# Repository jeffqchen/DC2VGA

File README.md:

# DC2VGA

An SD/VGA RGBS/RGBHV Switchable Dongle for Sega Dreamcast.

This belongs to my [series of VGA adapters](https://github.com/jeffqchen/Console-VGA-Dongle-Series) for various retro consoles and video equipments.

This adapter plugs into the AV OUT port on a Sega Dreamcast and allows you to out put RGBS or RGBHV video signal, as well as a stereo audio signal.

------------
## Usage

### Toggling Modes

There are two independent toggle switches on this dongle for choosing different modes.

- SD / VGA allows you to choose between 525i (SD) and 525p (VGA) RGB output
- CSYNC / HV allows you to choose between attenuated CSync and 3.3V H/V-Sync

I have tested this dongle with various devices:

|              | SD+CSync | VGA+CSync | SD+HV  | VGA+HV    |
|--------------|----------|-----------|--------|-----------|
| RetroTINK 5X | **Yes**  | **Yes**   | No     | No        |
| OSSC (AV3)   | Yes*     | **Yes**   | **Yes**| **Yes**   |
| GBS Control  | **Yes**  | **Yes**   | Yes*   | Yes*      |
| PVM/BVM      | **Yes**  | [*Maybe*](https://github.com/jeffqchen/DC2VGA#combined-csync)  | No     | No        |
| PC Monitors  | No       | No        | No     | **Yes**   |

The No ones are mostly device limitations and not a problem with the dongle itself.

The Yes* ones means they only work when the signal first went through an Extron switch. It's probably that the switch reconditioned the signals in some way to overcome the limitations of these devices and made things work. A direct connection does not work in these cases and it's expected.

The only real compatibility issue I've encountered so far, is **VGA** mode + **CSync** on Sony BVM D series. This BVM doesn't like combined CSync and will not display it properly. **However it will work properly in SD mode.**

#### *VGA Trick*

*(Bust-A-Move 4 tricked into run in VGA mode)*

Some games that require an SD cable can be forced into VGA mode by toggling the top switch from SD to VGA, right after booting up the game (at the VMU beep or right after game started from the ODE).

### Audio

Audio can be carried inside the VGA cable as-is, or extracted from the 3.5mm jack on the dongle.

* *Buzzing may be noticeable when audio is transmitted within the VGA cable in certain scenes in certain games. This is due to insufficient shielding in most VGA cables. If you find the buzzing to be annoying, use the 3.5mm jack on the dongle for audio output. This will ensure the cleanest possible audio.*

### Other Use Cases

Light guns work if you output to a CRT display (TV and PC monitor).

 -----------

 ## Parts

- PCB (You need both)
  - [Vertical PCB](https://oshpark.com/shared_projects/WcKgCnij)
  - [Horizontal PCB](https://oshpark.com/shared_projects/jPAbQ0ej)

- [1x] Dreamcast AV Plugs - [Link](https://github.com/jeffqchen/JeffParts/blob/main/Connectors/Dreamcast%20AV%20Plug/info.md)

- [2x] Toggle Switches (SW1 & SW2) - [Link](https://github.com/jeffqchen/JeffParts/tree/main/Switches/EG2208%20Toggle%20Switch/info.md)
  - *If you want slightly longer switch stems, use **EG2208A** instead.*

- [1x] VGA Port Slim Female - [Link](https://github.com/jeffqchen/JeffParts/blob/main/Connectors/HD15/Slim/Female%20PCB/info.md)

- [1x] 3.5mm Headphone Jack - [Link](https://github.com/jeffqchen/JeffParts/blob/main/Connectors/3.5mm%20Audio%20Jack/Vertical%205-Pin%20PCB/info.md)

- [1x] M2x20mm screw and hex nut - [Link](https://github.com/jeffqchen/JeffParts/blob/main/Parts/M2%20M3%20Hex%20Screw%20%26%20Nut/info.md)

- 2.54mm-Pitched Right Angle Pin Header (at least 11-pin wide) - [Link](https://github.com/jeffqchen/JeffParts/blob/main/Connectors/Pin%20Header/2.54mm%20Pitch/Male%20Right-Angle/info.md)

### SMD Components

*All SMD resistors and capacitors are in imperial 0603 size unless specified otherwise*

#### On Vertical Board
- **U1**: [1x] 4-Channel XOR Logic Gate, 14TSSOP
  - MC74HC86ADTR2G Quad XOR Gate - [[Link](https://github.com/jeffqchen/JeffParts/blob/main/Components/MC74HC86ADTR2G%20Quad%20XOR%20Gate/info.md)]
- **C1 C2 C3**: [3x] 220uF / 6.3V / **Imperial 1206 Size** - [[Link](https://github.com/jeffqchen/JeffParts/blob/main/Components/220uF%20SMD%20Cap/info.md)]
- **C4**: [1x] 0.1uF / 10V
- **C5 C6**: [2x] ]1uF / 10V
- **R1 R2**: [2x] 150 Ohm
- **R3 R4**: [2x] 10K Ohm

**R5 and R6** can have different configurations. Choose one from the following:
- For 0.6V Vpp CSync: (common attenuated CSync level)
  - R5: 25 Ohm
  - R6: 680 Ohm

- For 0.3V Vpp CSync: (SCART-safe sync level)
  - R5: 75 Ohm
  - R6: 1K Ohm

#### On Horizontal Board
- C1 C2: [2x] 10uF / 6.3V

-----------

## 3D Printing

Print all parts in their original orientations.

The shells are printed on the 3.5mm port side to give it a flat surface on that side and better details on the top.

Try using tree support as it's easier to extract and leaves less damage to up-facing surfaces below supported surfaces.

Make sure all support material is removed before trying to fit the electronics inside, as there is zero space to spare inside.

### Without A Shell

Thanks to [Retro Gamer Stuff](https://twitter.com/RetroGamerStuff)'s suggestion, I've adopted right-angle pin headers to interconnect the two PCBs with a very reliable connection. This means the internal assembly should be able to sustain even without a shell. It will be unsightly, but should be strong enough regardless.

-----------

## Preparations

### Dreamcast Video Plug

The original Dreamcast video plug has a cross bar to prevent the pins from falling out. You need to extract it with a side cutter or dental pick like shown in the picture. Try prying from the center of the bar so it lifts cleanly.

*IF* a pin falls out during the process, simply carefully push it back into its original place.

Put the printed "Plug Helper" piece over the pins. Note the correct side of the slot. Then push it all the way into the back of the plug until it's flush.

This piece helps to maintain a leveled surface so the plug can be soldered to the PCB reliably.

### PCB

Trim extra tabs sticking outside from the PCB outline with a side-cutter and file. Otherwise you may run into issues trying to fit the assembly into the 3D printed shell.

-----------

## Assembly

Populate the horizontal and vertical PCBs with all of the SMD components first.

Solder in the Dreamcast video plug and the switches onto the "DC Side" of the vertical board.

Note the DC video plug should be perpendicular to the vertical PCB.

There is an area of exposed copper next to the DC video plug. You can add some solder in this area to further strengthen the connection between the plug and the PCB. However it's only optional.

Cut a section of the pin header with 11 pins. Fit the bent end onto the horizontal PCB from the bottom side, as close as possible. Then solder in the two ends first.

You can adjust the pin header by melting the two ends. Make sure the straight part of the pin header is parallel to the PCB as much as possible.

Now start trimming out the extra length of the pins on the bent end. Make it as flush as possible to the PCB. Do the unsoldered pins in the middle first, then solder the flush pins to the PCB.

Lastly, suck up any excessive solder from the two end pins, and then trim them flush as well.

Using a cutter, cut and remove the black plastic piece that holds all the pins together. Try cutting in with a light angle so the cuts reach the pins for an easy removal.

Now solder in the VGA and 3.5mm port tightly onto the horizontal PCB.

Trim the 3 pins that would be blocked by the toggle switch. Refer to the photos for an easier way to get it done.

Temporarily fit the entire assembly into the top shell. Position the PCBs so the 3.5mm port and VGA port fits into the cutouts on the top shell snugly, and the vertical PCB is as vertical as possible.

 Solder the 3 trimmed pins and the one on the other end, to hold the assembly together.

Take the assembly out of the 3D printed shell. We do NOT want to do a lot of soldering when the assembly is inside the shell, or the heat may damage it.

Go on and trim all the rest of the excessive straight pins and solder them in place. Feed an ample amount of solder and heat up the pin long enough so the solder could seep into the vias on the vertical PCB.

Inspect the other side and make sure the vias are filled by solder. If not, heat it up again with a bit more solder. The internal assembly is now finished.

Now, fit the completed internals into the bottom shell, then put the top shell over it and close it up.

Secure the shells with a set of M2x20mm screw and nut.

------------
## Some Technical Nuances

### Native CSync

This Dongle uses the native CSync signal generated by the Dreamcast itself - when it's set to SD mode. This mode has the best compatibility with SD TVs and monitors.

### Combined CSync

When set to VGA mode **AND** CSync, the circuit inside uses an XOR logic chip to combine the native HSync and VSync signals into an artificial CSync signal. This signal has a slight discrepancy from a standard CSync signal, and some equipments that rely on PLL (phase lock loop) would be thrown off (as documented in the [HDRetrovision Blog](https://www.hdretrovision.com/blog/2019/10/10/engineering-csync-part-2-falling-short)).

This issue was anticipated and since in most cases, you would not run into any issue, I opted to not dig deeper and further complicate the design.

#### Proper Sync Combining

However, if you are stuck with a rare display that absolutely requires proper sync combining, you may look into Extron's RGB 19X line of product.

They feature proper sync combining with serration. This will fix the CSync issue IF your device refuse to work with the rough method. At this moment, it's only listed for around $30 on eBay. It's a very good value in my personal opinion, as this device can work with a various range of VGA devices and resolutions.

Set the DC2VGA to "HV" mode, connect the VGA cable to the Extron RGB, set SERR and DDSP to the UP position, connect the BNC cables to the R/G/B/S ports on the back, and the issue should be fixed.

*The audio adapter in the 2nd photo is my [Extron Audio 3.5mm Adapter](https://github.com/jeffqchen/Extron-Audio-3.5mm-Adapter).*

### OSSC AV3 Input Limitations

The AV3 input on the OSSC require clean TTL-level sync signals. However the native CSync output from the Dreamcast is an attenuated one. This signal does not work with the OSSC and is expected.

*Source: [OSSC Wiki](https://junkerhq.net/xrgb/index.php/OSSC#AV3_.28VGA.29)*

### GBS Control Limitations
The GBS 82XX board does not work nicely with VGA signals. [Robert Neumann](https://twitter.com/_ramapcsx2) put in some time hoping to make it work but decided it's not a suitable use case for the GBS board. So the RGBHV signal coming from the Dreamcast not working with GBS is expect. You should always use CSync instead.

### Improved Compatibility with Extron switches
By running the signal through an Extron MVX Switch, several of the incompatibilities mentioned above could be overcome. It probably thanks to the extra signal conditioning it performances on the inside. These Extron devices are lovely.

**But you should always remember that they output 5V TTL sync and that needs to be properly attenuated if connected to a consumer device.**

-----------
## Special Thanks
Mike Chi
- Twitter: https://twitter.com/retrotink2
- Official Website: https://www.retrotink.com/

HDRetrovision
- Twitter: https://twitter.com/hdretrovision
- Official Website: https://www.hdretrovision.com/

Javier Rodas
- Twitter: https://twitter.com/JaviRodasG

Robert Neumann
- Twitter: https://twitter.com/_ramapcsx2

Retro Gamer Stuff (Bad_Ad84)
- https://twitter.com/RetroGamerStuff

-----------
Shield: [![CC BY-SA 4.0][cc-by-sa-shield]][cc-by-sa]

This work is licensed under a
[Creative Commons Attribution-ShareAlike 4.0 International License][cc-by-sa].

[![CC BY-SA 4.0][cc-by-sa-image]][cc-by-sa]

[cc-by-sa]: http://creativecommons.org/licenses/by-sa/4.0/
[cc-by-sa-image]: https://licensebuttons.net/l/by-sa/4.0/88x31.png
[cc-by-sa-shield]: https://img.shields.io/badge/License-CC%20BY--SA%204.0-lightgrey.svg

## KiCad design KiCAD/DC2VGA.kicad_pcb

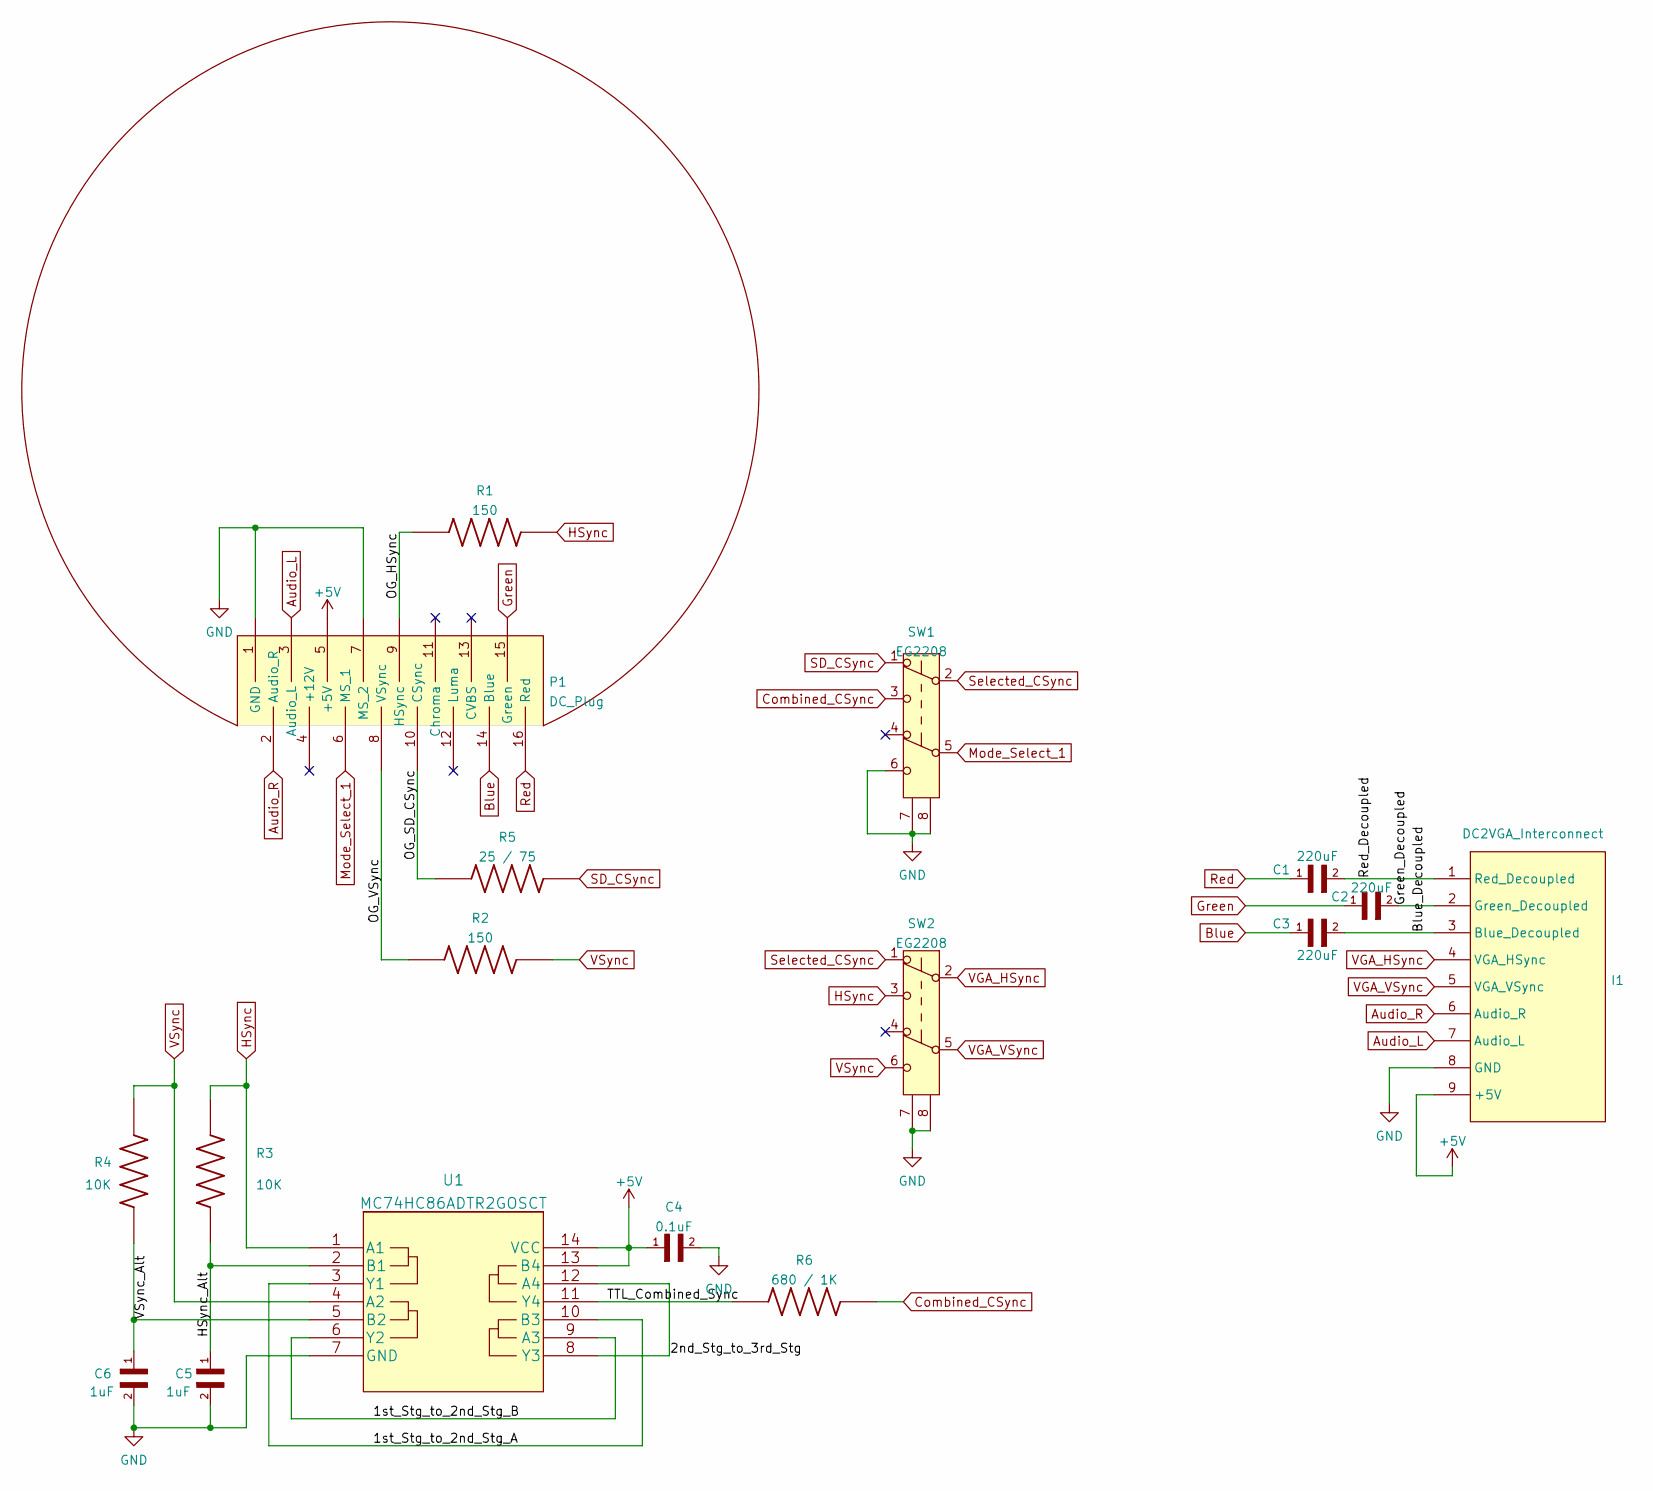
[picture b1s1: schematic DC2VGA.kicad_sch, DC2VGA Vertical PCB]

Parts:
C1, C2, C3: 220uF; Cap_SMD_1206
C4: 0.1uF; C_0603_1608Metric
C5, C6: 1uF; C_0603_1608Metric
I1: DC2VGA_Interconnect; DC_Interconnect_Vertical
P1: DC_Plug
R1, R2: 150; R_0603_1608Metric
R3, R4: 10K; R_0603_1608Metric
R5: 25 / 75; R_0603_1608Metric
R6: 680 / 1K; R_0603_1608Metric
SW1, SW2: EG2208; EG2208_DPDT_Switch
U1: MC74HC86ADTR2GOSCT; MC74HC86

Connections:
+5V: C4.1, I1.9 (+5V), P1.5 (+5V), U1.13 (B4), U1.14 (VCC)
/1st_Stg_to_2nd_Stg_A: U1.3 (Y1), U1.10 (B3)
/1st_Stg_to_2nd_Stg_B: U1.6 (Y2), U1.9 (A3)
/2nd_Stg_to_3rd_Stg: U1.8 (Y3), U1.12 (A4)
/Blue_Decoupled: C3.2, I1.3 (Blue_Decoupled)
/Green_Decoupled: C2.2, I1.2 (Green_Decoupled)
/HSync_Alt: C5.1, R3.1, U1.2 (B1)
/OG_Combined_Sync: R6.1, U1.11 (Y4)
/OG_HSync: P1.9 (HSync), R1.1
/OG_SD_CSync: P1.10 (CSync), R5.1
/OG_VSync: P1.8 (VSync), R2.1
/Red_Decoupled: C1.2, I1.1 (Red_Decoupled)
/VSync_Alt: C6.1, R4.2, U1.5 (B2)
Audio_L: I1.7 (Audio_L), P1.3 (Audio_L)
Audio_R: I1.6 (Audio_R), P1.2 (Audio_R)
Blue: C3.1, P1.14 (Blue)
Combined_CSync: R6.2, SW1.3 (C)
GND: C4.2, C5.2, C6.2, I1.8 (GND), P1.1 (GND), P1.7 (MS_2), SW1.6 (C), SW1.7 (Shield), SW1.8 (GND), SW2.7 (Shield), SW2.8 (GND), U1.7 (GND)
Green: C2.1, P1.15 (Green)
HSync: R1.2, R3.2, SW2.3 (C), U1.1 (A1)
Mode_Select_1: P1.6 (MS_1), SW1.5 (B)
Red: C1.1, P1.16 (Red)
SD_CSync: R5.2, SW1.1 (A)
Selected_CSync: SW1.2 (B), SW2.1 (A)
VGA_HSync: I1.4 (VGA_HSync), SW2.2 (B)
VGA_VSync: I1.5 (VGA_VSync), SW2.5 (B)
VSync: R2.2, R4.1, SW2.6 (C), U1.4 (A2)

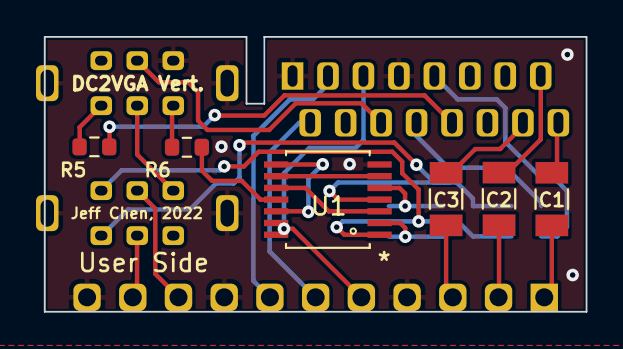
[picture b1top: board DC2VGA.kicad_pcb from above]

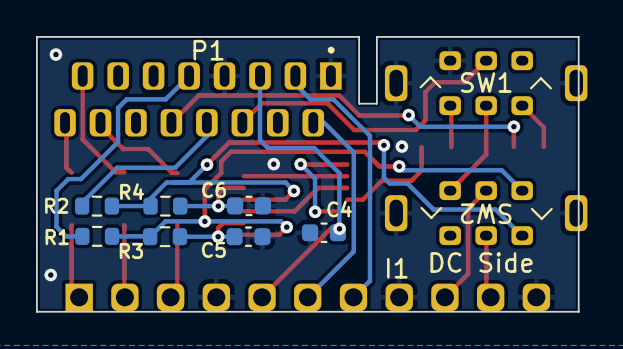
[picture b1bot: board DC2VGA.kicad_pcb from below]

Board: 2 copper layers, 30.1 x 15.3 mm, 17 parts (11 on the bottom side), 27 nets.

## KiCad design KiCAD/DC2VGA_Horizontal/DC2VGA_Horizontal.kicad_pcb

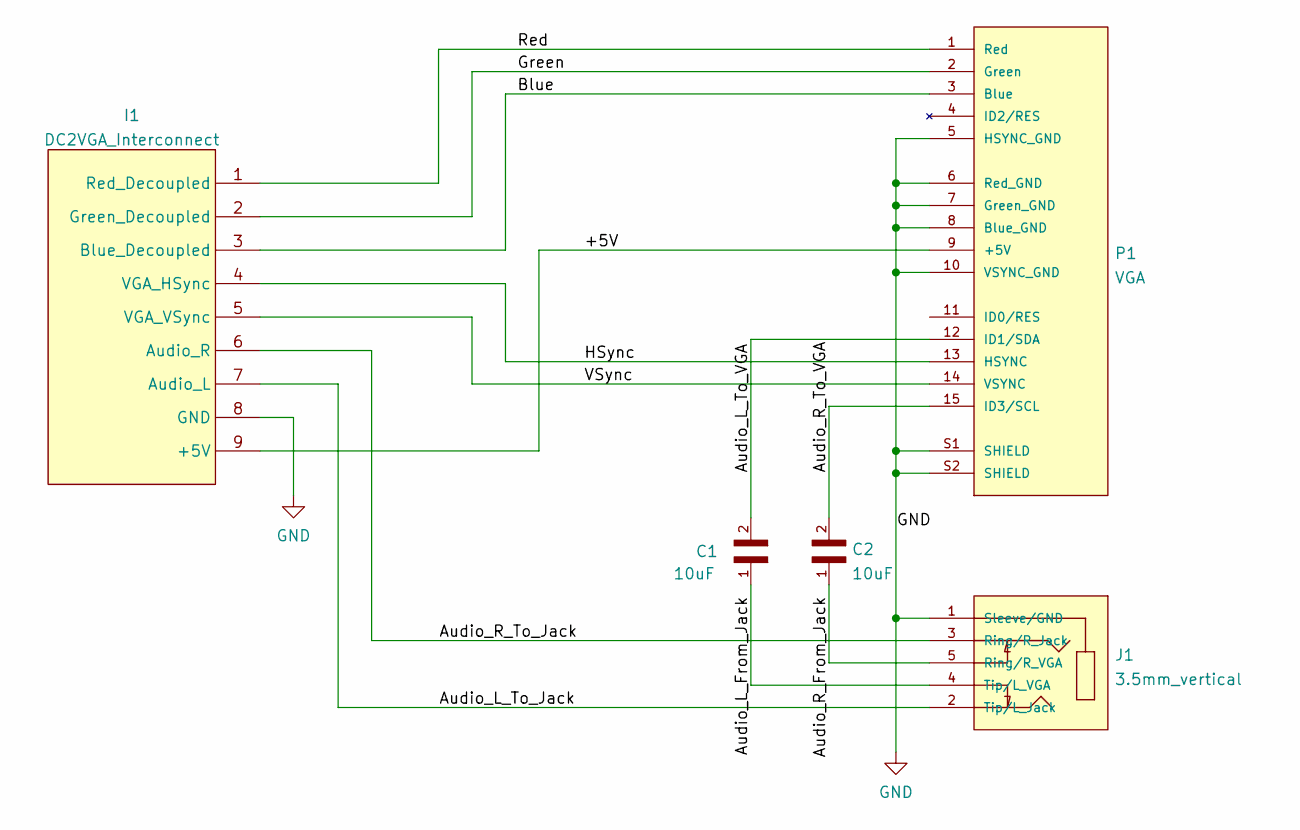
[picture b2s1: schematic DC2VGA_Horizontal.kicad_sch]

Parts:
C1, C2: 10uF; C_0603_1608Metric
I1: DC2VGA_Interconnect; DC_Interconnect_Horizontal
J1: 3.5mm_vertical
P1: VGA; VGA_female_rightangle_slim; PARTREV N/A

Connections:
/+5V: I1.9 (+5V), P1.9 (+5V)
/Audio_L_From_Jack: C1.1, J1.4 (Tip/L_VGA)
/Audio_L_To_Jack: I1.7 (Audio_L), J1.2 (Tip/L_Jack)
/Audio_L_To_VGA: C1.2, P1.12 (ID1/SDA)
/Audio_R_From_Jack: C2.1, J1.5 (Ring/R_VGA)
/Audio_R_To_Jack: I1.6 (Audio_R), J1.3 (Ring/R_Jack)
/Audio_R_To_VGA: C2.2, P1.15 (ID3/SCL)
/Blue: I1.3 (Blue_Decoupled), P1.3 (Blue)
/Green: I1.2 (Green_Decoupled), P1.2 (Green)
/HSync: I1.4 (VGA_HSync), P1.13 (HSYNC)
/Red: I1.1 (Red_Decoupled), P1.1 (Red)
/VSync: I1.5 (VGA_VSync), P1.14 (VSYNC)
GND: I1.8 (GND), J1.1 (Sleeve/GND), P1.5 (HSYNC_GND), P1.6 (Red_GND), P1.7 (Green_GND), P1.8 (Blue_GND), P1.10 (VSYNC_GND), P1.S1 (SHIELD), P1.S2 (SHIELD)

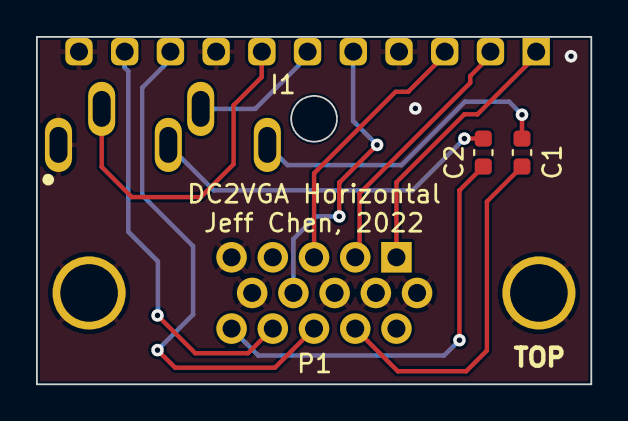
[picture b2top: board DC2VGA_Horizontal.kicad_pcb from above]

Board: 2 copper layers, 30.8 x 19.3 mm, 5 parts (0 on the bottom side), 13 nets.

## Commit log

2022-03-20 3D print images
2022-03-20 Add pics
2022-03-22 Update 2.54 URL
2022-08-09 Change license type
2022-08-19 Add Info of Extron 19X for Sync Combining

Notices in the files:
parts and their libraries:
Copyright 2021 Accelerated Designs. All rights reserved.
